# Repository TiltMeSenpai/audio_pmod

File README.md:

NOTE:

This pmod currently has not been manufactured or tested.
Use at your own risk.

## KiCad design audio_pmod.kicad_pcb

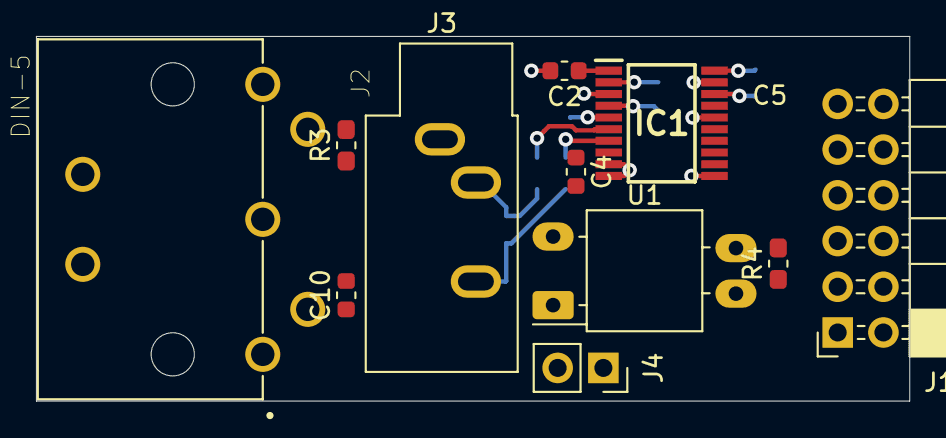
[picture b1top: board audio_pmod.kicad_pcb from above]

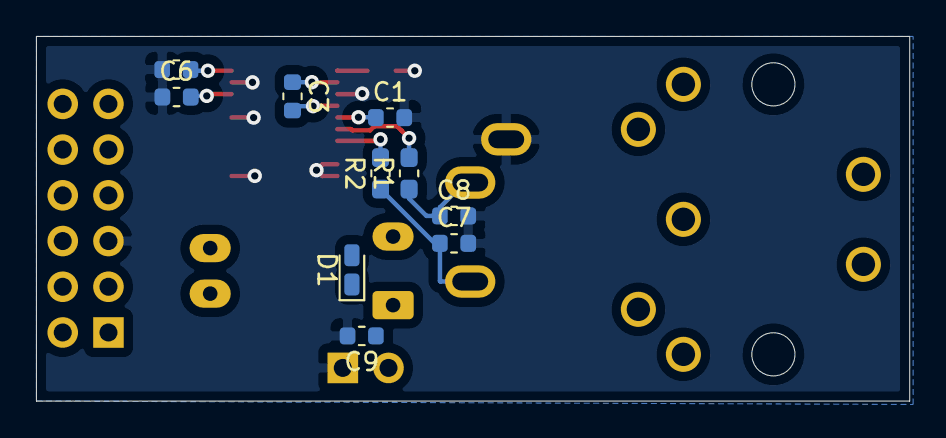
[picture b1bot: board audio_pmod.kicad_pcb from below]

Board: 2 copper layers, 48.5 x 20.3 mm, 21 parts (10 on the bottom side), 20 nets.

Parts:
C1, C2, C3, C4, C5, C6, C9, C10: C; C_0603_1608Metric
C7, C8: 2.2nf; C_0603_1608Metric
D1: D; D_0603_1608Metric_Castellated
IC1: PCM5100APW; SOP65P640X120-20N
J1: Conn_02x06_Counter_Clockwise; PinSocket_2x06_P2.54mm_Horizontal
J2: DIN-5; CUI_SDS-50J
J3: AudioJack3; Jack_3.5mm_CUI_SJ1-3533NG_Horizontal
J4: Conn_01x02; PinSocket_1x02_P2.54mm_Vertical
R1, R2, R3, R4: R; R_0603_1608Metric_Pad1.05x0.95mm_HandSolder
U1: NSL-32; Luna_NSL-32

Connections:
BCK: IC1.13, J1.10
DIN: IC1.14, J1.11
GND: C1.2, C2.2, C4.2, C5.2, C6.1, C7.2, C8.2, C9.2, C10.2, IC1.3, IC1.9, IC1.10, IC1.11, IC1.16, IC1.19, J1.5, J1.8, J3.S, J4.1
LRCLK: IC1.15, J1.12
MIDI_IN: J1.1, R4.1
unnamed: C1.1, IC1.5
unnamed: C3.1, IC1.2
unnamed: C3.2, IC1.4
unnamed: C6.2, IC1.18
unnamed: C7.1, J3.R, R2.1
unnamed: C8.1, J3.T, R1.1
unnamed: D1.2, R3.1, U1.2
unnamed: J2.5, R3.2
unnamed: R4.2, U1.3
OUTL: IC1.6, R1.2
OUTR: IC1.7, R2.2
SCK: IC1.12, J1.9
VBUS: C9.1, C10.1, D1.1, J2.4, J4.2, U1.1
VCC: C2.1, C4.1, C5.1, IC1.1, IC1.8, IC1.20, J1.6, J1.7, U1.4
~MUTE: IC1.17, J1.2

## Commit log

2020-01-31 Init
2020-01-31 Add readme
